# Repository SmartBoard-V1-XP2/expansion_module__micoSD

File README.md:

# Expansion Module: MicroSD Card Slot

## Overview
The *Expansion Module: MicroSD Card Slot* is designed for interfacing with FPGA on the SmartBoard platform. It provides a slot for a microSD card, enabling the module to facilitate easy data storage and retrieval. This module is an excellent tool for learning about and experimenting with microSD interfacing.

### Key Features
- MicroSD card slot for simple and efficient data storage.
- Compatible with SmartBoard's single socket interface.
- Ideal for applications and learning experiences in microSD card interfacing.

## Design Files

### Schematic Diagram

### Board Layout

## License
The *Expansion Module: MicroSD Card Slot* project is released under the MIT License, granting permission to use, modify, and distribute this design in both private and commercial settings.

- **Permission to Use**: You are free to use, modify, and distribute this design in both private and commercial settings.
- **Attribution Requirement**: While not required, attribution to the original author, Adam Łuczak, is appreciated. This can be done through a citation or a link back to this repository.
- **No Warranty**: This design is provided "as is", without warranty of any kind. Use it at your own risk.
- **Liability**: The author is not liable for any damages or losses that may arise from the use of this design.

For the full terms and conditions, please refer to the MIT License documentation.

## Contact
For any inquiries or suggestions about the *Expansion Module: MicroSD Card Slot* project, please feel free to contact Adam Łuczak at adam.luczak@outlook.com.

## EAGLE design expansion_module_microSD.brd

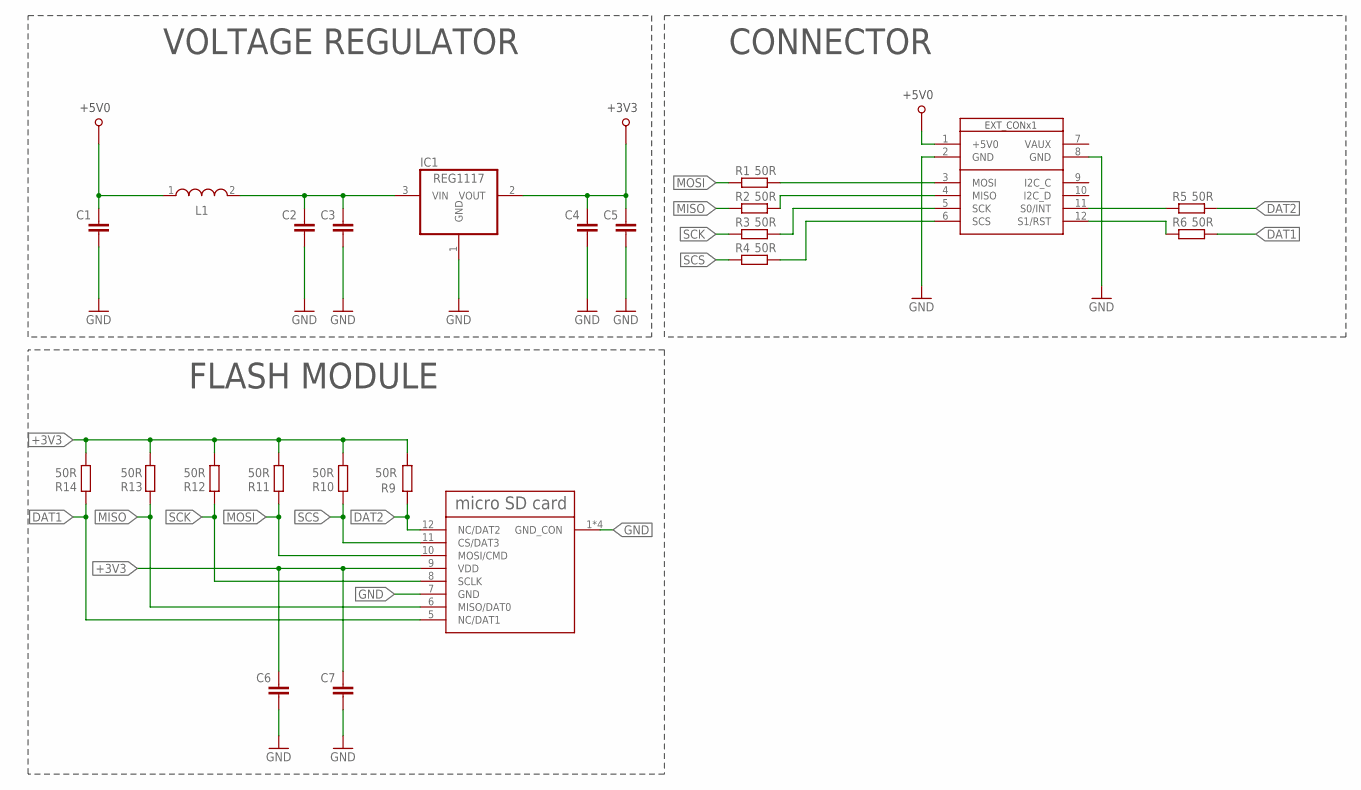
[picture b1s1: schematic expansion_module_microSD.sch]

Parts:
C1, C2, C3, C4, C5, C6, C7: C-EUC0805; C0805
IC1: REG1117; SOT223
L1: WE-LQ_1210; WE-LQ_M
MICRO_SD_CARD: MX5009010801
R1, R2, R3, R4, R5, R6, R9, R10, R11, R12, R13, R14: 50R; R0805
U$1: SB_EXT_CON_X1_SPI; SB_EXT_CON_X1_FULL

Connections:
+3V3: C4.2, C5.2, C6.2, C7.2, IC1.2 (VOUT), MICRO_SD_CARD.9 (VDD), R9.2, R10.2, R11.2, R12.2, R13.2, R14.2
+5V0: C1.2, L1.1, U$1.1 (+5V0)
DAT1: MICRO_SD_CARD.5 (NC/DAT1), R6.2, R14.1
DAT2: MICRO_SD_CARD.12 (NC/DAT2), R5.2, R9.1
GND: C1.1, C2.1, C3.1, C4.1, C5.1, C6.1, C7.1, IC1.1 (GND), MICRO_SD_CARD.1 (GND_CON), MICRO_SD_CARD.2 (GND_CON), MICRO_SD_CARD.3 (GND_CON), MICRO_SD_CARD.4 (GND_CON), MICRO_SD_CARD.7 (GND), U$1.2 (GND), U$1.8 (GND)
MISO: MICRO_SD_CARD.6 (MISO/DAT0), R2.1, R13.1
MOSI: MICRO_SD_CARD.10 (MOSI/CMD), R1.1, R11.1
unnamed: R1.2, U$1.3 (MOSI)
unnamed: R2.2, U$1.4 (MISO)
unnamed: R3.2, U$1.5 (SCK)
unnamed: R4.2, U$1.6 (SCS)
unnamed: R5.1, U$1.11 (S0/INT)
unnamed: R6.1, U$1.12 (S1/RST)
unnamed: C2.2, C3.2, IC1.3 (VIN), L1.2
SCK: MICRO_SD_CARD.8 (SCLK), R3.1, R12.1
SCS: MICRO_SD_CARD.11 (CS/DAT3), R4.1, R10.1

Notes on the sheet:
CONNECTOR
VOLTAGE REGULATOR
FLASH MODULE

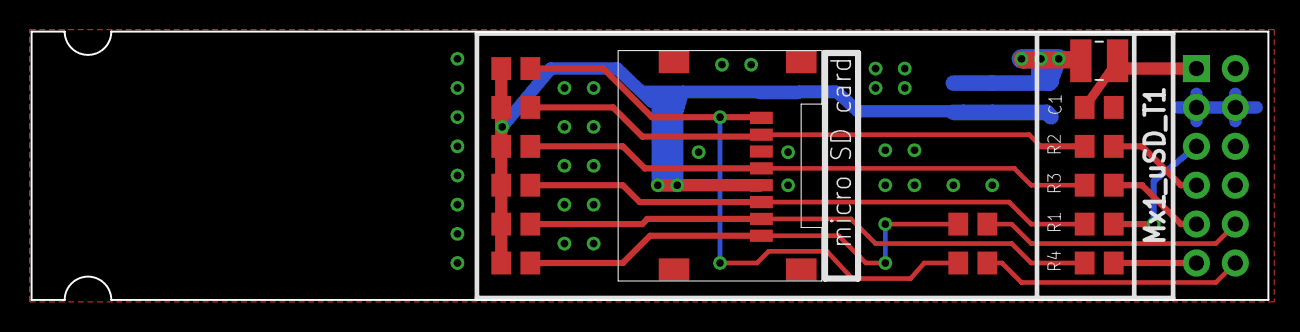
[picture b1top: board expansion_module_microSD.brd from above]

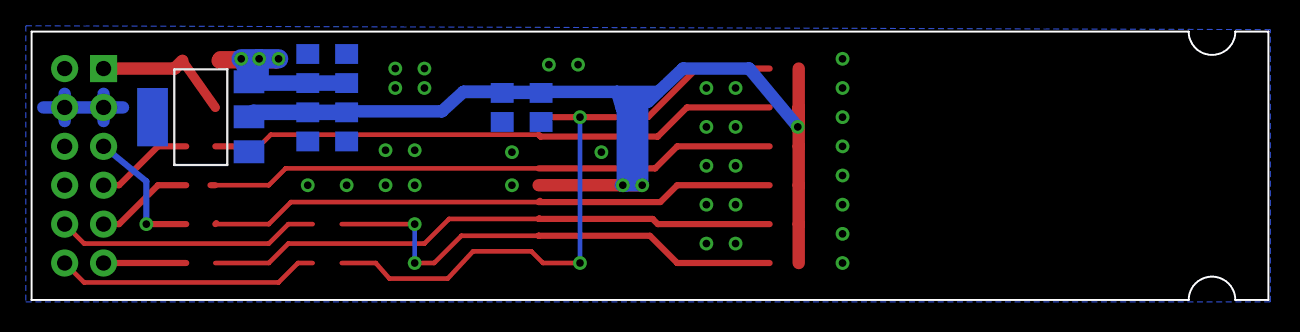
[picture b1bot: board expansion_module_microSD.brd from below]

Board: 2 copper layers, 80.8 x 17.5 mm, 23 parts (7 on the bottom side), 16 nets.

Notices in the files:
README.md:
License: MIT
parts and their libraries:
EagleLibrary_Wuerth_Elektronik_eiSos_rev: Copyright: Würth Elektronik
